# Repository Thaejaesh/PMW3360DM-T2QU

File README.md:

# FORKED FROM ORIGINAL CREATOR : Good-Great-Grand-Wonderful @ https://github.com/Good-Great-Grand-Wonderful/PMW3360DM-T2QU

# PMW3360DM-T2QU
High-quality pointing for your keyboard projects.

## Bill of materials

| Qty | Item                        | Description           |
|-----|-----------------------------|-----------------------|
| 1x  | PMW3360DM-T2QU              | Trackball sensor      |
| 3x  | 1uF 0402 Capacitor          |                       |
| 1x  | 4.7uF/10V 0402 Capacitor    |                       |
| 1x  | 39ohm 0402 Resistor 0402    |                       |
| 1x  | 10k 0402 Resistor           |                       |
| 1x  | TLV74318PDBVR               | LDO Voltage Regulator |
| 1x  | SM06B-SRSS-TB(LF)(SN)       | JST SH 6P Connector   |
| 2x  | M3 Brass Inserts            |                       |
| 3x  | 3mmx6mmx2.5mm Ball Bearings |                       |
| 3x  | 3mmx6mm Allen Set Screws    |                       |
| 2x  | M3x12 Bolts                 |                       |
| 1x  | Top carrier                 | Available in `models` |
| 1x  | Base carrier                | Available in `models` |

### Assembly

This board contains small components. While hand soldering is possible, I highly recommend a PCBA service. Gerbers, BOM, and CPL are all available in the Releases section. Choose to assemble the bottom of the PCB, and note that the sensor is intentionally omitted for both cost savings and the convenience of soldering at home.

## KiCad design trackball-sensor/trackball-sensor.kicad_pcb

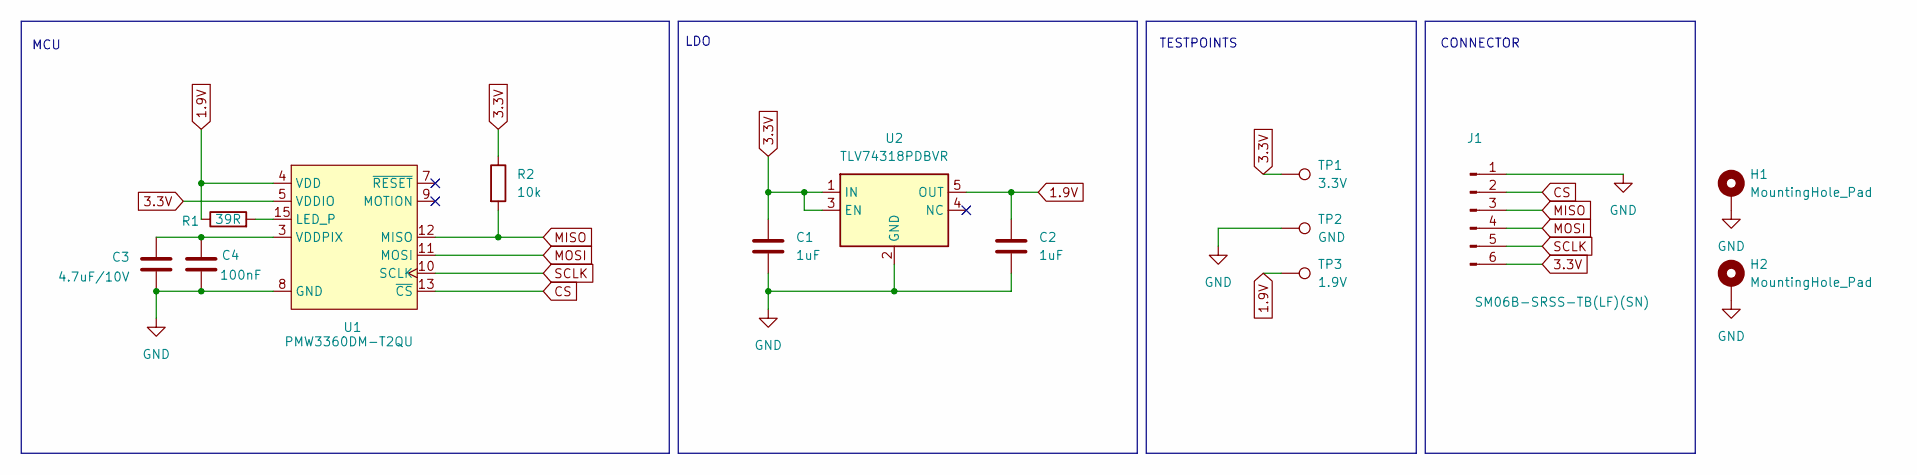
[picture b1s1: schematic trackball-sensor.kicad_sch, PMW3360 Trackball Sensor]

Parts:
C1, C2: 1uF; C_0402_1005Metric
C3: 4.7uF/10V; C_0402_1005Metric
C4: 100nF; C_0402_1005Metric
H1, H2: MountingHole_Pad; MountingHole_3.2mm_M3_Pad
J1: SM06B-SRSS-TB(LF)(SN)
R1: 39R; R_0402_1005Metric
R2: 10k; R_0402_1005Metric
TP1: 3.3V; TestPoint_Pad_D1.5mm
TP2: GND; TestPoint_Pad_D1.5mm
TP3: 1.9V; TestPoint_Pad_D1.5mm
U1: PMW3360DM-T2QU; PMW3360DM-T2QU 16Pin
U2: TLV74318PDBVR; SOT-23-5

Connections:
1.9V: C2.1, R1.1, TP3.1, U1.4 (VDD), U2.5 (OUT)
3.3V: C1.1, J1.6, R2.1, TP1.1, U1.5 (VDDIO), U2.1 (IN), U2.3 (EN)
CS: J1.2, U1.13 (~CS)
GND: C1.2, C2.2, C3.2, C4.2, H1.1, H2.1, J1.1, TP2.1, U1.8 (GND), U2.2 (GND)
MISO: J1.3, R2.2, U1.12 (MISO)
MOSI: J1.4, U1.11 (MOSI)
unnamed: R1.2, U1.15 (LED_P)
unnamed: C3.1, C4.1, U1.3 (VDDPIX)
SCLK: J1.5, U1.10 (SCLK)

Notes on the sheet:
MCU
LDO
TESTPOINTS
CONNECTOR

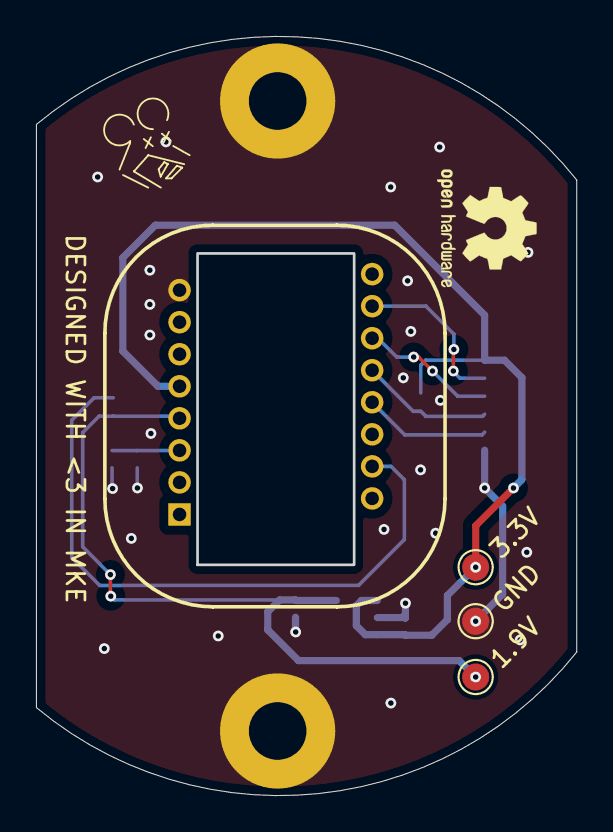
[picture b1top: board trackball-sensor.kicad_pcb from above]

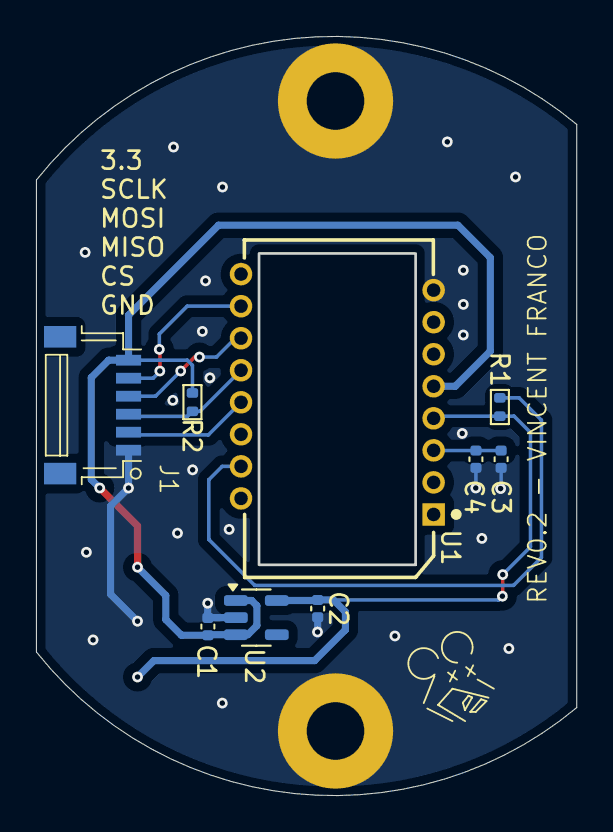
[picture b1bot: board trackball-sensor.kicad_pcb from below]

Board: 2 copper layers, 29.9 x 42.1 mm, 14 parts (9 on the bottom side), 9 nets.

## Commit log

2024-12-06 Adding KiCad files
2024-12-06 Adding models
2024-12-06 Fixup models
2024-12-11 Added license, updating model
2024-12-11 Add ignore
2024-12-29 [PATCH] Increasing trackball height by 1mm
2025-01-09 Adding indicator to help with assembly
2025-01-16 Adjusting roller bearing hole from 3.1mm to 3.0mm
2025-02-25 Adding static bearing models
2025-04-01 Updating carrier base
